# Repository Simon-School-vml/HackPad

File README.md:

# HackPad
A macro pad made with sponsering from amd and hackclub.
# The Design
Here is the schematic design of my macropad.

And here is the PCB layout and traces.

The pcb 3d models from Kicad

And for the case I used onshape because I know how it works and have used it allot!
I have created a 4 part case (I know very complex) for the astetics and also to have it tilted at a slight angle for comfort.

# BOM

for this very lovely keypad you need a few components.

1. PCB custom made
2. Xiao RP2040
3. 16x MX style switches (any of your flavor)
4. 16x Keycaps
5. 16x diode 1n4148
6. 16x SK6812 MINI-E LEDs
7. 0.91 inch OLED display

M3 mounting hardware
4x M3x22-25 (for case)
3x M3x6     (for PCB)

3D printed parts
the four parts from the step file

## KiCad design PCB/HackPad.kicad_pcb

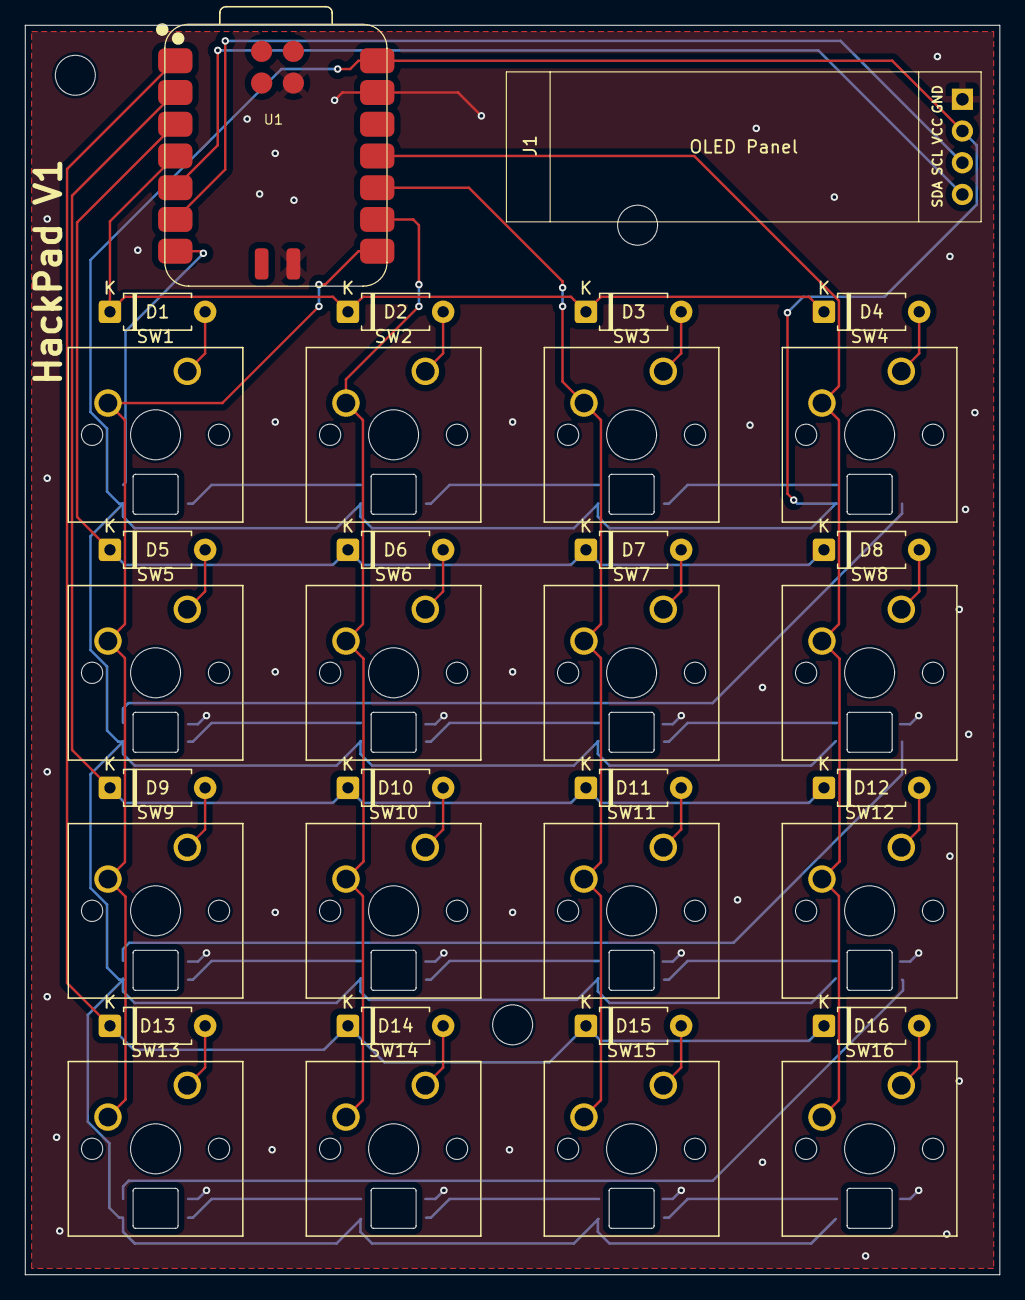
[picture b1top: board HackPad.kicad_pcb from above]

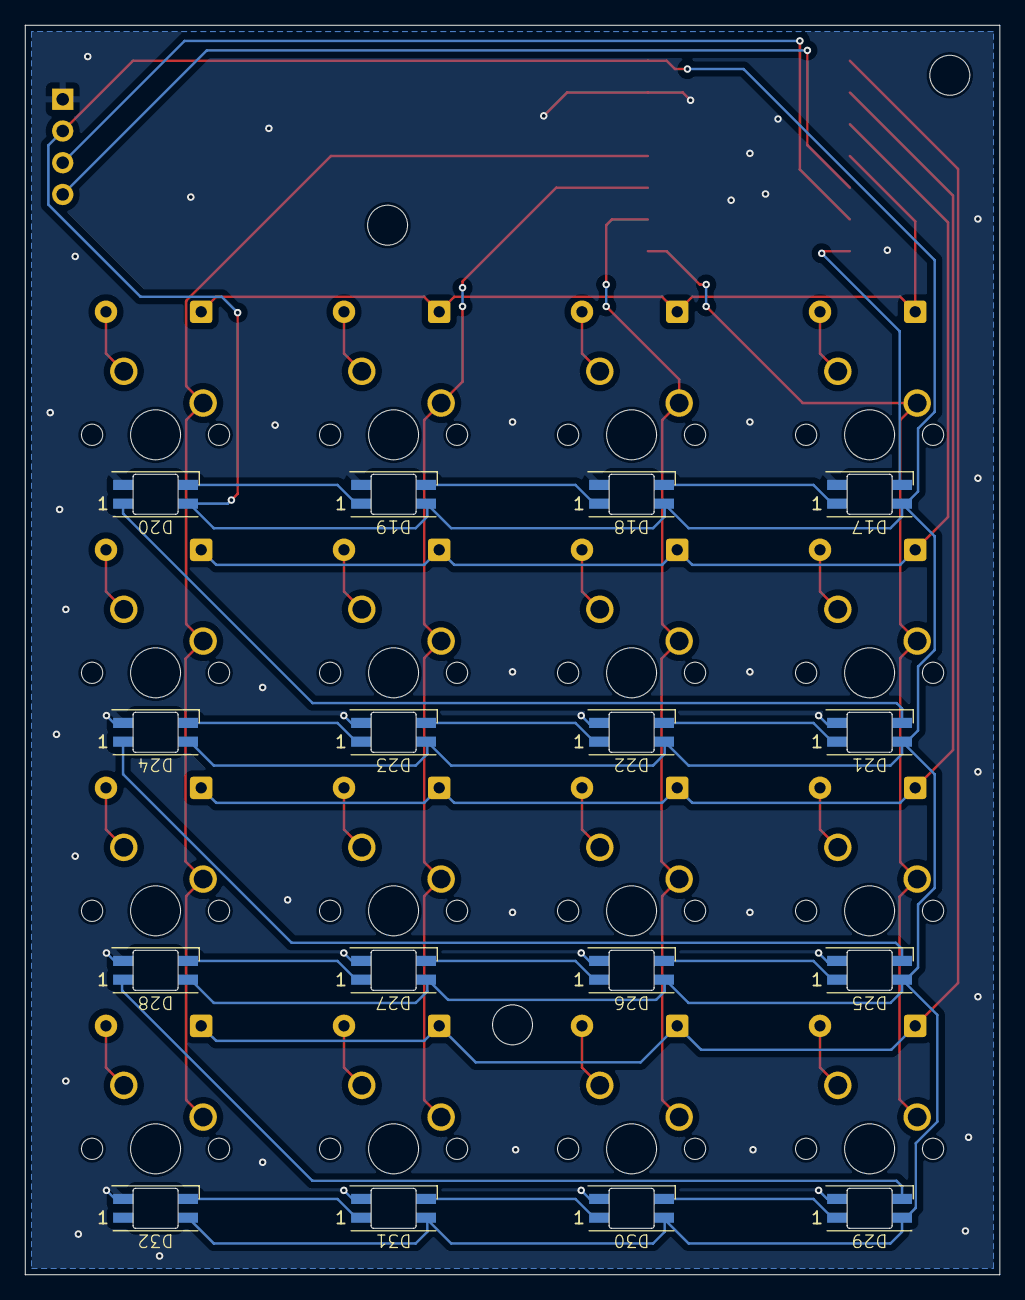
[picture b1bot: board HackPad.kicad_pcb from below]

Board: 2 copper layers, 78.0 x 100.0 mm, 50 parts (16 on the bottom side), 44 nets.

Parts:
D1, D2, D3, D4, D5, D6, D7, D8, D9, D10, D11, D12, D13, D14, D15, D16: 1N4148; D_A-405_P7.62mm_Horizontal
D17, D18, D19, D20, D21, D22, D23, D24, D25, D26, D27, D28, D29, D30, D31, D32: SK6812MINI; LED_SK6812MINI-E_PLCC4_3.2x2.8mm_P1.5mm
J1: 0.91 OLED Display; SSD1306-0.91-OLED-4pin-128x32
SW1, SW2, SW3, SW4, SW5, SW6, SW7, SW8, SW9, SW10, SW11, SW12, SW13, SW14, SW15, SW16: MX; SW_Cherry_MX_1.00u_PCB
U1: XIAO-RP2040-SMD

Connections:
COL1: SW1.2, SW5.2, SW9.2, SW13.2, U1.8 (GPIO1_D7_CSn_RX)
COL2: SW2.2, SW6.2, SW10.2, SW14.2, U1.9 (GPIO2_D8_SCK)
COL3: SW3.2, SW7.2, SW11.2, SW15.2, U1.10 (GPIO4_D9_MISO)
COL4: SW4.2, SW8.2, SW12.2, SW16.2, U1.11 (GPIO3_D10_MOSI)
GND: D17.2 (VSS), D18.2 (VSS), D19.2 (VSS), D20.2 (VSS), D21.2 (VSS), D22.2 (VSS), D23.2 (VSS), D24.2 (VSS), D25.2 (VSS), D26.2 (VSS), D27.2 (VSS), D28.2 (VSS), D29.2 (VSS), D30.2 (VSS), D31.2 (VSS), D32.2 (VSS), J1.1, U1.13 (GND), U1.16 (GND), U1.20 (GND)
LEDs: D17.3 (DIN), U1.7 (GPIO0_D6_TX)
unnamed: D1.2 (A), SW1.1
unnamed: D2.2 (A), SW2.1
unnamed: D3.2 (A), SW3.1
unnamed: D4.2 (A), SW4.1
unnamed: D5.2 (A), SW5.1
unnamed: D6.2 (A), SW6.1
unnamed: D7.2 (A), SW7.1
unnamed: D8.2 (A), SW8.1
unnamed: D9.2 (A), SW9.1
unnamed: D10.2 (A), SW10.1
unnamed: D11.2 (A), SW11.1
unnamed: D12.2 (A), SW12.1
unnamed: D13.2 (A), SW13.1
unnamed: D14.2 (A), SW14.1
unnamed: D15.2 (A), SW15.1
unnamed: D16.2 (A), SW16.1
unnamed: D17.1 (DOUT), D18.3 (DIN)
unnamed: D18.1 (DOUT), D19.3 (DIN)
unnamed: D19.1 (DOUT), D20.3 (DIN)
unnamed: D20.1 (DOUT), D21.3 (DIN)
unnamed: D21.1 (DOUT), D22.3 (DIN)
unnamed: D22.1 (DOUT), D23.3 (DIN)
unnamed: D23.1 (DOUT), D24.3 (DIN)
unnamed: D24.1 (DOUT), D25.3 (DIN)
unnamed: D25.1 (DOUT), D26.3 (DIN)
unnamed: D26.1 (DOUT), D27.3 (DIN)
unnamed: D27.1 (DOUT), D28.3 (DIN)
unnamed: D28.1 (DOUT), D29.3 (DIN)
unnamed: D29.1 (DOUT), D30.3 (DIN)
unnamed: D30.1 (DOUT), D31.3 (DIN)
unnamed: D31.1 (DOUT), D32.3 (DIN)
ROW1: D1.1 (K), D2.1 (K), D3.1 (K), D4.1 (K), U1.4 (GPIO29_A3_D3)
ROW2: D5.1 (K), D6.1 (K), D7.1 (K), D8.1 (K), U1.3 (GPIO28_A2_D2)
ROW3: D9.1 (K), D10.1 (K), D11.1 (K), D12.1 (K), U1.2 (GPIO27_A1_D1)
ROW4: D13.1 (K), D14.1 (K), D15.1 (K), D16.1 (K), U1.1 (GPIO26_A0_D0)
SCL: J1.3, U1.6 (GPIO7_D5_SCL)
SDA: J1.4, U1.5 (GPIO6_D4_SDA)
VBUS: D17.4 (VDD), D18.4 (VDD), D19.4 (VDD), D20.4 (VDD), D21.4 (VDD), D22.4 (VDD), D23.4 (VDD), D24.4 (VDD), D25.4 (VDD), D26.4 (VDD), D27.4 (VDD), D28.4 (VDD), D29.4 (VDD), D30.4 (VDD), D31.4 (VDD), D32.4 (VDD), J1.2, U1.14 (5V)

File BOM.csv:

Designator,Footprint,Quantity,Value,Price,Source
,,,,,
"SW1, SW2, SW3, SW4, SW5, SW6, SW7, SW8, SW9, SW10, SW11, SW12, SW13, SW14, SW15, SW16",SW_Cherry_MX_1.00u_PCB,16,SW_Push,Included,Hackclub
U1,XIAO-RP2040-SMD,1,XIAO-RP2040-SMD,Included,Hackclub
"D1, D2, D3, D4, D5, D6, D7, D8, D9, D10, D11, D12, D13, D14, D15, D16",Diode_THT:D_A-405_P7.62mm_Horizontal,16,1N4148,Included,Hackclub
"D17, D18, D19, D20, D21, D22, D23, D24, D25, D26, D27, D28, D29, D30, D31, D32",SK6812MINI-E,16,SK6812MINI,Included,Hackclub
J1,0.91 OLED Display,1,0.91 OLED Display,Included,Hackclub
PCB  (JLCPCB),,1,, 4.24,www.jlcpcb.com
3D printed parts,,1,,Free,Printer at home
,,,,,
,,,,grand total  4.24,

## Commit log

2025-11-29 Create CAD
